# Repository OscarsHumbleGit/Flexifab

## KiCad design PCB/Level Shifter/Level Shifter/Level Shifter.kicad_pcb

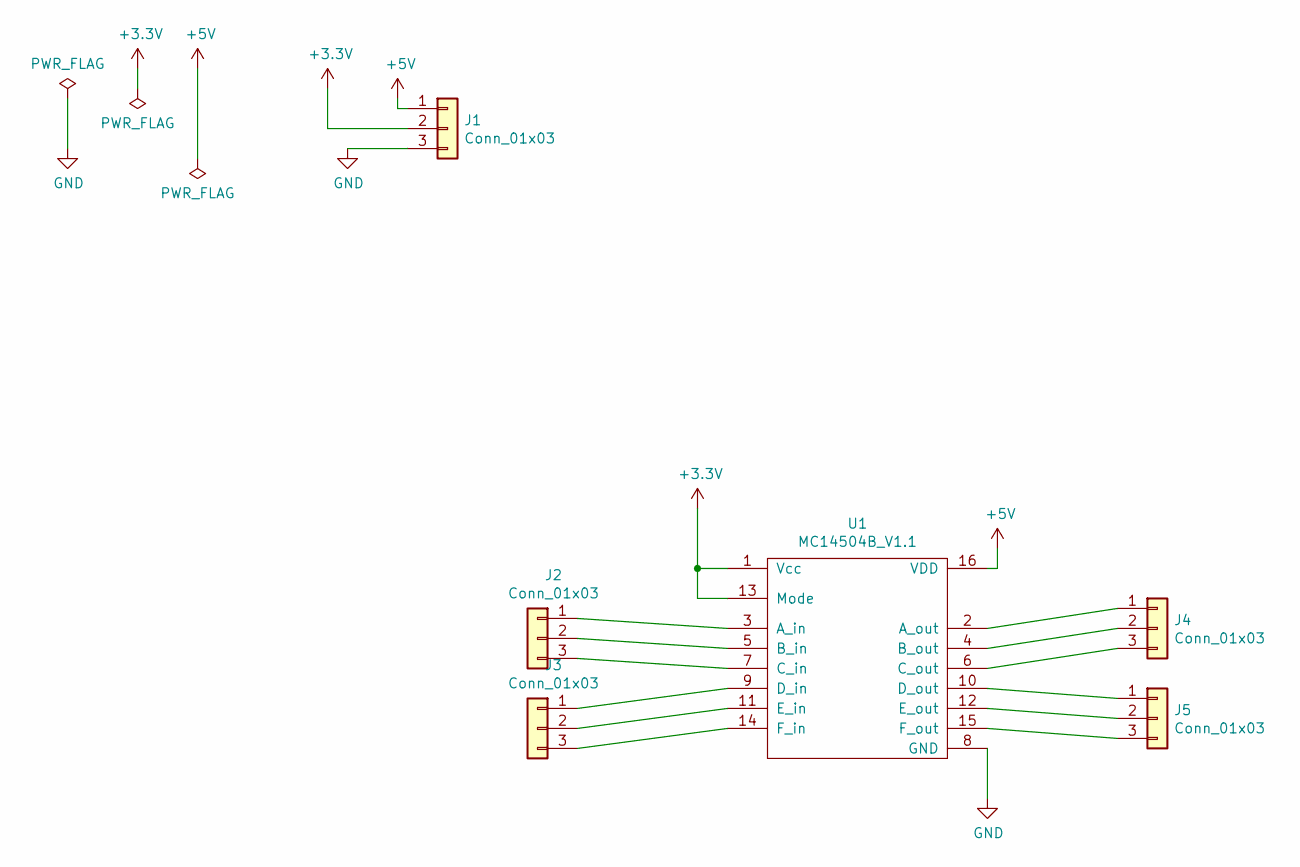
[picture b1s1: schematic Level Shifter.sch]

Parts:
J1, J2, J3, J4, J5: Conn_01x03; Molex_KK-6410-03_03x2.54mm_Straight
U1: MC14504B_V1.1; MC14504B

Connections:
+3V3: J1.2, U1.1 (Vcc), U1.13 (Mode)
+5V: J1.1, U1.16 (VDD)
GND: J1.3, U1.8 (GND)
unnamed: J2.1, U1.3 (A_in)
unnamed: J2.2, U1.5 (B_in)
unnamed: J2.3, U1.7 (C_in)
unnamed: J3.1, U1.9 (D_in)
unnamed: J3.2, U1.11 (E_in)
unnamed: J3.3, U1.14 (F_in)
unnamed: J4.1, U1.2 (A_out)
unnamed: J4.2, U1.4 (B_out)
unnamed: J4.3, U1.6 (C_out)
unnamed: J5.1, U1.10 (D_out)
unnamed: J5.2, U1.12 (E_out)
unnamed: J5.3, U1.15 (F_out)

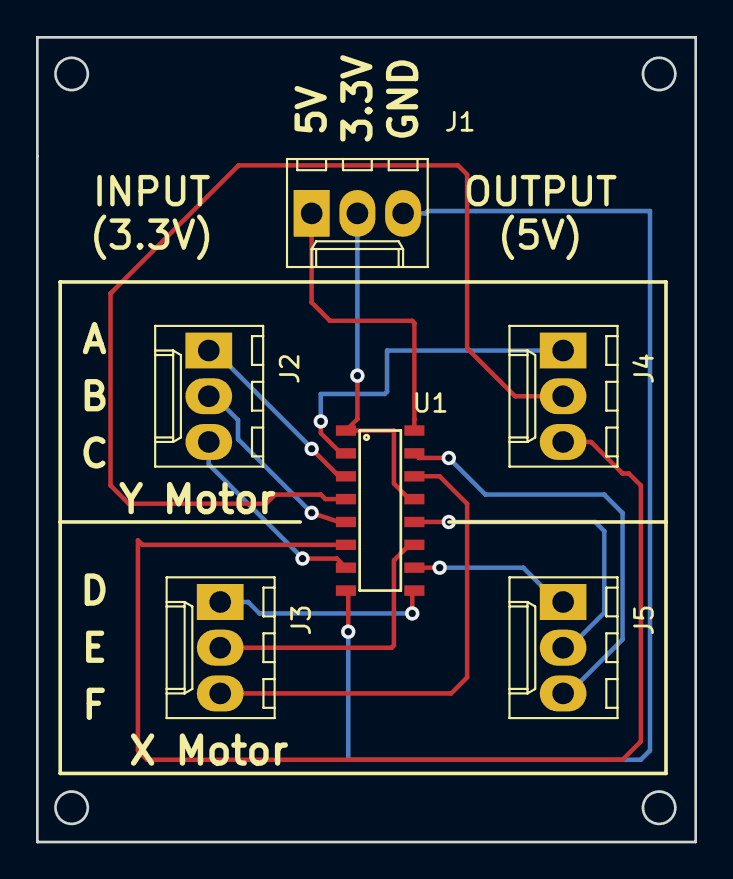
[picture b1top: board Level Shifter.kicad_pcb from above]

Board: 2 copper layers, 36.6 x 44.7 mm, 6 parts (0 on the bottom side), 15 nets.

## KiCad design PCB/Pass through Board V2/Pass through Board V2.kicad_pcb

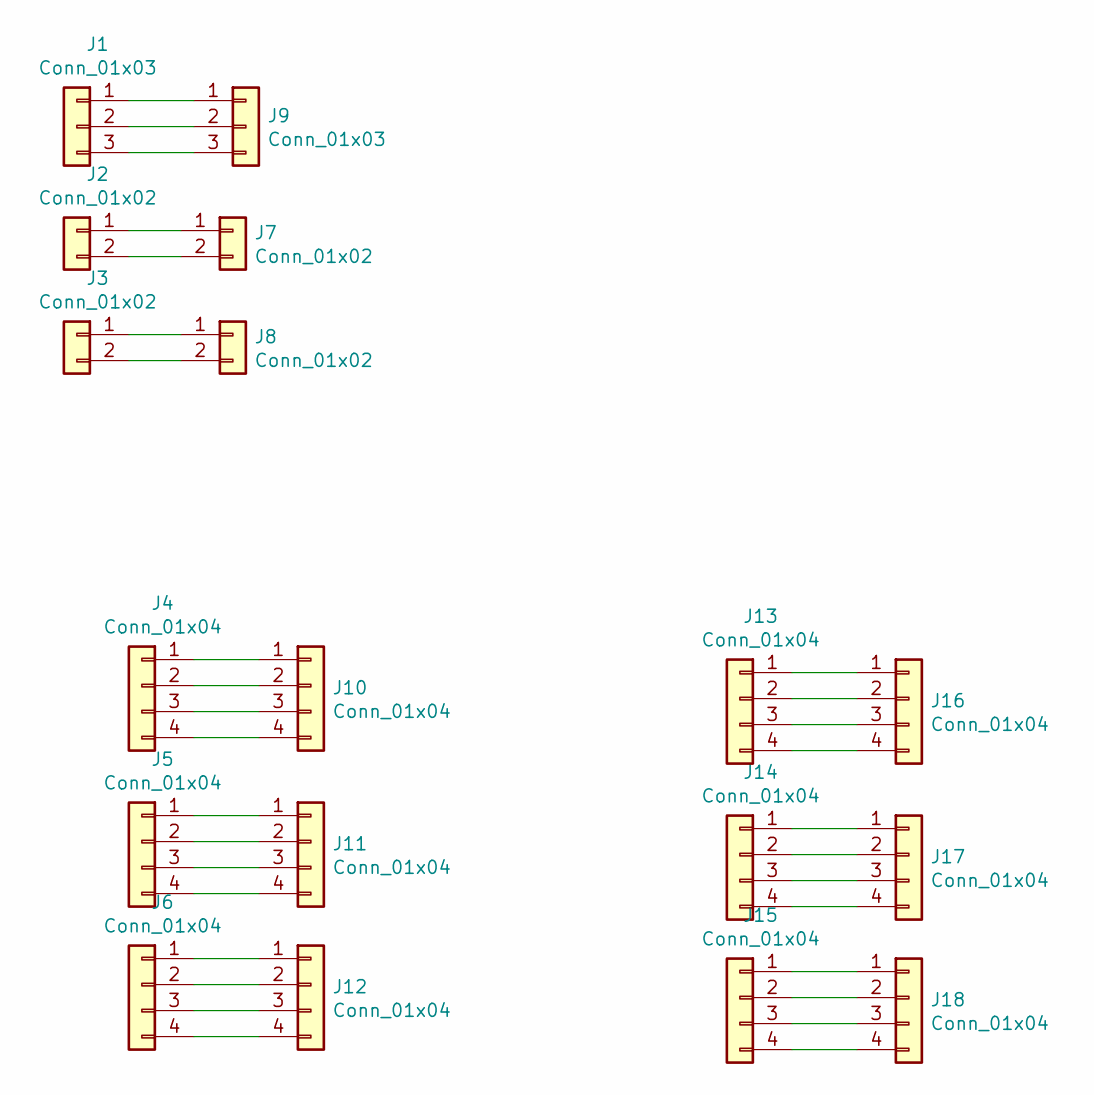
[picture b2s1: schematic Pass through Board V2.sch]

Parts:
J1, J9: Conn_01x03; Molex_KK-6410-03_03x2.54mm_Straight
J2, J3, J7, J8: Conn_01x02; Molex_KK-6410-02_02x2.54mm_Straight
J4, J5, J6, J10, J11, J12, J13, J14, J15, J16, J17, J18: Conn_01x04; Molex_KK-6410-04_04x2.54mm_Straight

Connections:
unnamed: J1.1, J9.1
unnamed: J1.2, J9.2
unnamed: J1.3, J9.3
unnamed: J2.1, J7.1
unnamed: J2.2, J7.2
unnamed: J3.1, J8.1
unnamed: J3.2, J8.2
unnamed: J4.1, J10.1
unnamed: J4.2, J10.2
unnamed: J4.3, J10.3
unnamed: J4.4, J10.4
unnamed: J5.1, J11.1
unnamed: J5.2, J11.2
unnamed: J5.3, J11.3
unnamed: J5.4, J11.4
unnamed: J6.1, J12.1
unnamed: J6.2, J12.2
unnamed: J6.3, J12.3
unnamed: J6.4, J12.4
unnamed: J13.1, J16.1
unnamed: J13.2, J16.2
unnamed: J13.3, J16.3
unnamed: J13.4, J16.4
unnamed: J14.1, J17.1
unnamed: J14.2, J17.2
unnamed: J14.3, J17.3
unnamed: J14.4, J17.4
unnamed: J15.1, J18.1
unnamed: J15.2, J18.2
unnamed: J15.3, J18.3
unnamed: J15.4, J18.4

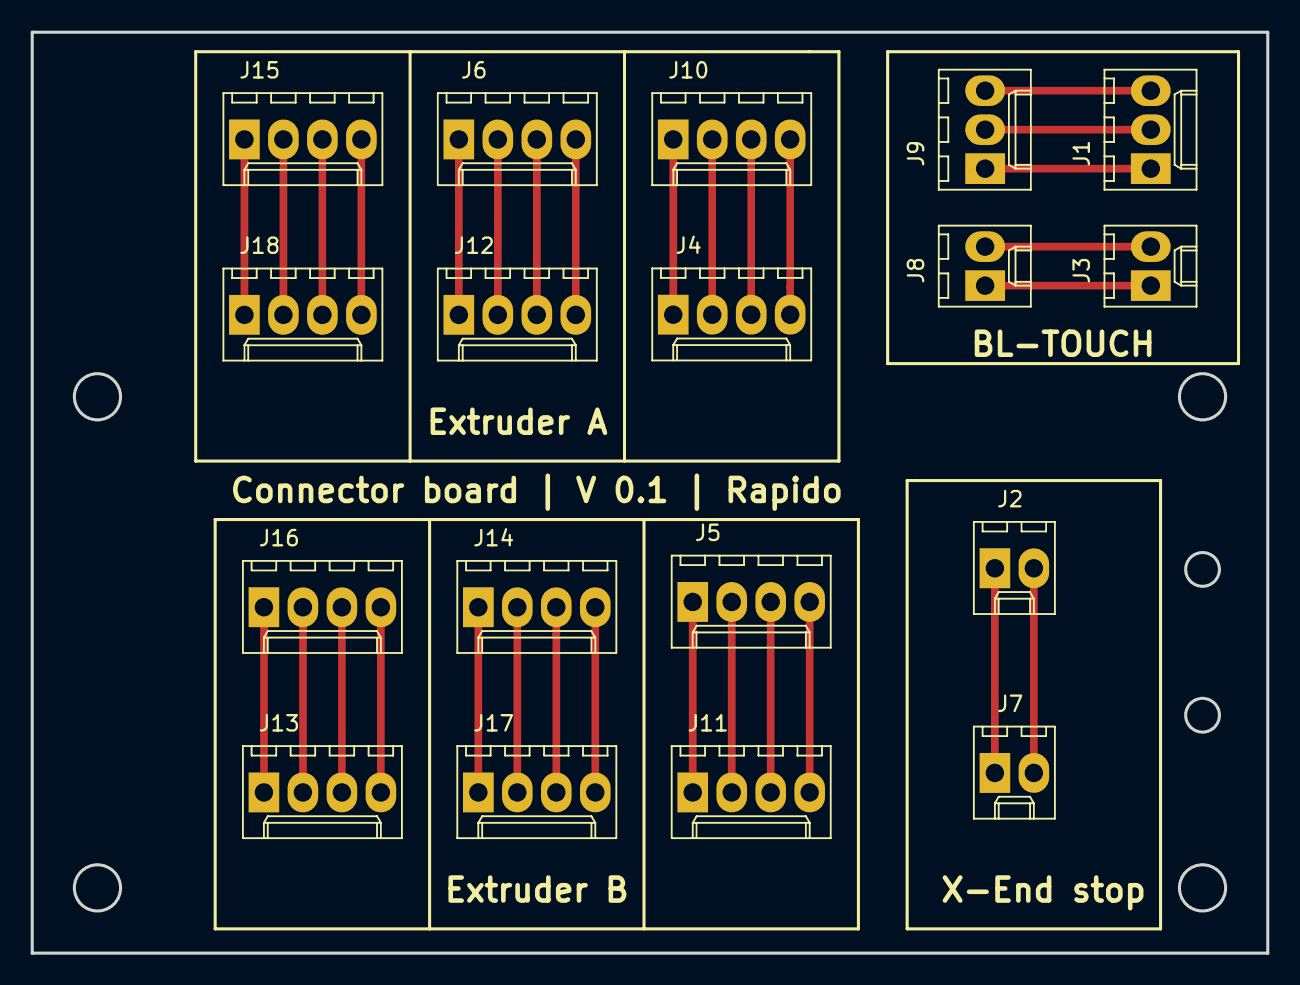
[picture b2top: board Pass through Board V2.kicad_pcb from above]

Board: 2 copper layers, 80.5 x 60.0 mm, 18 parts (0 on the bottom side), 31 nets.

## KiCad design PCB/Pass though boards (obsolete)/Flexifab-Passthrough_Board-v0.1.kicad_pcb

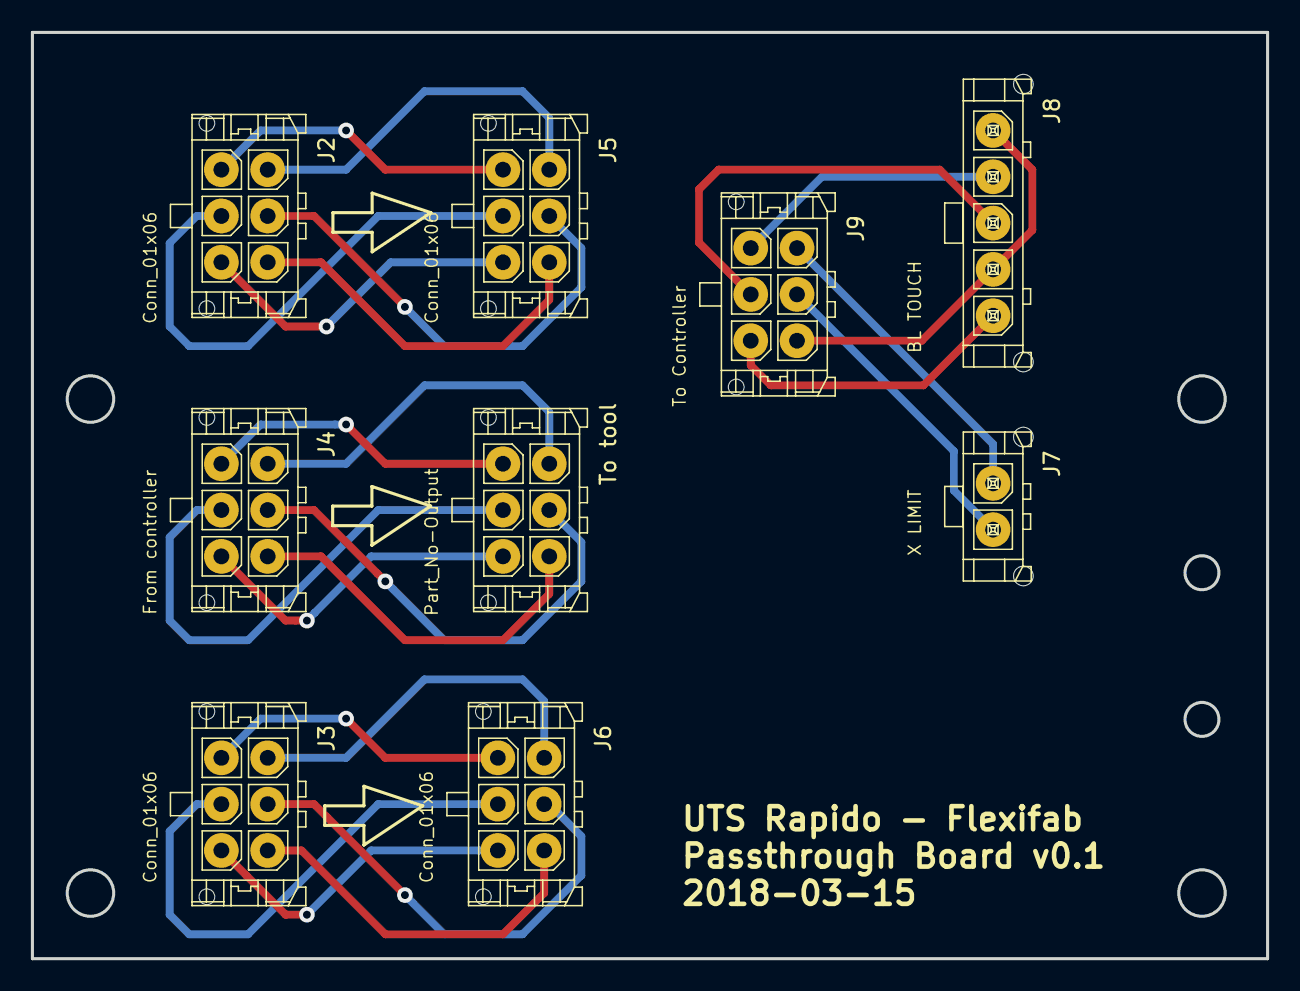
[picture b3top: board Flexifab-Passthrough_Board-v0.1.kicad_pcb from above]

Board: 2 copper layers, 80.0 x 60.0 mm, 9 parts (0 on the bottom side), 24 nets.

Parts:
J2, J3, J5, J6: Conn_01x06; Molex-43045-06##-Micro-Fit_3.00mm_Pitch_Vertical_Header-6Pin
J4: From controller; Molex-43045-06##-Micro-Fit_3.00mm_Pitch_Vertical_Header-6Pin
J7: X LIMIT; Molex-43650-02##-Micro-Fit_3.00mm_Pitch_Vertical_Single_Row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
J8: BL TOUCH; Molex-43650-05##-Micro-Fit_3.00mm_Pitch_Vertical_Single_Row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
J9: To Controller; Molex-43045-06##-Micro-Fit_3.00mm_Pitch_Vertical_Header-6Pin
To tool : Part_No-Output; Molex-43045-06##-Micro-Fit_3.00mm_Pitch_Vertical_Header-6Pin

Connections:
unnamed: J4.1, To tool.1
unnamed: J4.2, To tool.2
unnamed: J4.3, To tool.3
unnamed: J4.4, To tool.4
unnamed: J4.5, To tool.5
unnamed: J4.6, To tool.6
unnamed: J2.1, J5.1
unnamed: J2.2, J5.2
unnamed: J2.3, J5.3
unnamed: J2.4, J5.4
unnamed: J2.5, J5.5
unnamed: J2.6, J5.6
unnamed: J3.1, J6.1
unnamed: J3.2, J6.2
unnamed: J3.3, J6.3
unnamed: J3.4, J6.4
unnamed: J3.5, J6.5
unnamed: J3.6, J6.6
unnamed: J7.1, J9.1
unnamed: J7.2, J9.2
unnamed: J8.1, J8.4, J9.3
unnamed: J8.2, J9.4
unnamed: J8.3, J9.5
unnamed: J8.5, J9.6

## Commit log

2018-03-07 Create test
2018-03-08 new folder
2018-03-08 initial
2018-03-15 Build of the week 8
2018-03-25 Week after Dean preso
